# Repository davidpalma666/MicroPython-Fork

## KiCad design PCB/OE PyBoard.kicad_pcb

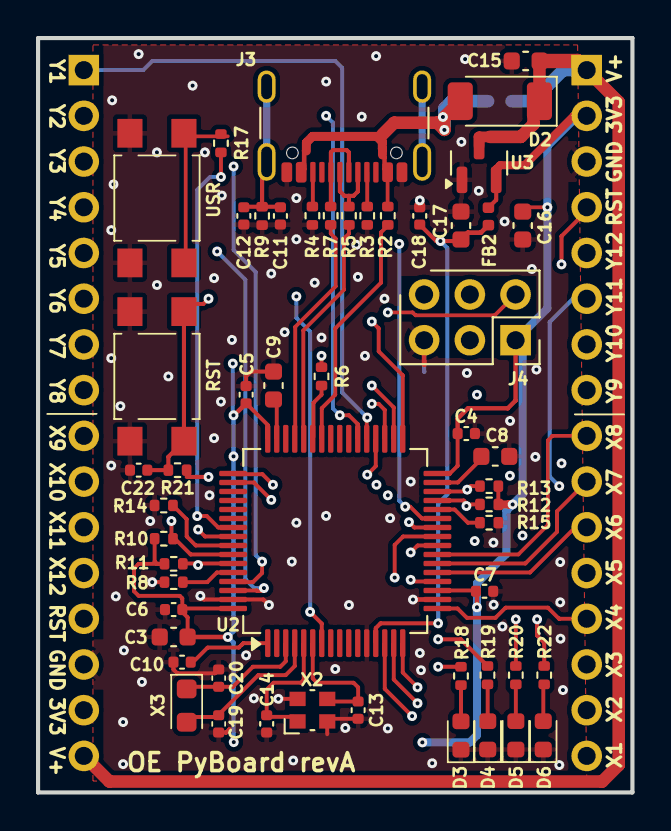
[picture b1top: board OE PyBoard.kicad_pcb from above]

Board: 4 copper layers, 33.0 x 41.9 mm, 56 parts (1 on the bottom side), 59 nets.

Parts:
C3, C16, C17: 4.7uF; C_0603_1608Metric
C4, C5, C6, C7, C10, C12, C18, C22: 100nF; C_0402_1005Metric
C8, C9, C15: 2.2uF; C_0603_1608Metric
C11: 4.7nF; C_0402_1005Metric
C13, C14, C19, C20: 12pF; C_0402_1005Metric
D2: SM5817PL; D_SOD-128
D3: LED-RED; LED_0603_1608Metric
D4: LED-GREEN; LED_0603_1608Metric
D5: LED-YELLOW; LED_0603_1608Metric
D6: LED-BLUE; LED_0603_1608Metric
FB2: 1k@100MHz; L_0402_1005Metric
J3: USB4105-GF-A; USB_C_Receptacle_GCT_USB4105-xx-A_16P_TopMnt_Horizontal
J4: Conn_02x03_Odd_Even; PinSocket_2x03_P2.54mm_Vertical
J6, J7: Conn_01x08; PinHeader_1x16_P2.54mm_Vertical
JP2: 0R; SolderJumper-2_P1.3mm_Open_RoundedPad1.0x1.5mm
R2, R18, R19, R20: 560R; R_0402_1005Metric
R3, R4: 5.1k; R_0402_1005Metric
R5, R7: 27R; R_0402_1005Metric
R6, R14, R15: 100k; R_0402_1005Metric
R8: 10k; R_0402_1005Metric
R9: 1M; R_0402_1005Metric
R10, R11, R12, R13, R17, R21: 4k7; R_0402_1005Metric
R22: 270R; R_0402_1005Metric
RST2: SW_SPST; SW_SPST_TL3305B
U2: STM32F405RGT6; LQFP-64_10x10mm_P0.5mm
U3: MCP1700T; SOT-23
USR2: SW_SPST; SW_SPST_TL3305B
X2: 12 MHz; Crystal_SMD_Abracon_ABM10-4Pin_2.5x2.0mm
X3: 32.768 kHz; Crystal_SMD_2012-2Pin_2.0x1.2mm_HandSoldering

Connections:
+3V3: C3.1, C4.1, C5.1, C6.1, C7.1, C16.1, FB2.1, J4.1, J6.15, J7.2, R6.1, R10.1, R11.1, R12.1, R13.1, R21.2, U2.19 (VDD), U2.32 (VDD), U2.48 (VDD), U2.64 (VDD), U3.2 (VO)
/B: D6.2 (A), R22.2
/BOOT0: R8.1, U2.60 (BOOT0)
/CC1: J3.A5 (CC1), R3.1
/CC2: J3.B5 (CC2), R4.1
/D+: J3.A6 (D+), J3.B6 (D+), R7.2
/D-: J3.A7 (D-), J3.B7 (D-), R5.2
/G: D4.2 (A), R19.2
/N1: C20.1, U2.3 (PC14-OSC32_IN), X3.1
/N2: C19.1, U2.4 (PC15-OSC32_OUT), X3.2
/N3: C14.1, U2.5 (PH0-OSC_IN), X2.1
/N4: C13.1, U2.6 (PH1-OSC_OUT), X2.3
/PA0-X1: J7.16, U2.14 (PA0)
/PA1-X2: J7.15, U2.15 (PA1)
/PA2-X3: J7.14, U2.16 (PA2)
/PA3-X4: J7.13, U2.17 (PA3)
/PA4-X5: J7.12, U2.20 (PA4)
/PA5-X6: J7.11, U2.21 (PA5)
/PA6-X7: J7.10, U2.22 (PA6)
/PA7-X8: J7.9, U2.23 (PA7)
/PA9-VBUS: R2.1, U2.42 (PA9)
/PA10-ID: R6.2, U2.43 (PA10)
/PA14-JTCK: J4.2, R19.1, U2.49 (PA14)
/PA15-JTDI: J4.6, R20.1, U2.50 (PA15)
/PB0-Y11: J7.6, U2.26 (PB0)
/PB1-Y12: J7.5, U2.27 (PB1)
/PB2-BOOT1-MMA-INT: R15.1, U2.28 (PB2)
/PB3-SW1: R17.1, U2.55 (PB3)
/PB4-NJTRST: J4.3, R22.1, U2.56 (PB4)
/PB5-MMA_AVDD: R14.1, U2.57 (PB5)
/PB6-JTDO: J4.4, R18.1
/PB6-SCL-X9: J6.9, R10.2, U2.58 (PB6)
/PB7-SDA-X10: J6.10, R11.2, U2.59 (PB7)
/PB8-Y3: J6.3, U2.61 (PB8)
/PB9-Y4: J6.4, U2.62 (PB9)
/PB10-Y9: J7.8, R12.2, U2.29 (PB10)
/PB11-Y10: J7.7, R13.2, U2.30 (PB11)
/PB12-Y5: J6.5, U2.33 (PB12)
/PB13-Y6: J6.6, U2.34 (PB13)
/PB14-Y7: J6.7, U2.35 (PB14)
/PB15-Y8: J6.8, U2.36 (PB15)
/PC4-X11: J6.11, U2.24 (PC4)
/PC5-X12: J6.12, U2.25 (PC5)
/PC6-Y1: J6.1, U2.37 (PC6)
/PC7-Y2: J6.2, U2.38 (PC7)
/R: D3.2 (A), R18.2
/RST-SW: C22.1, J6.13, J7.4, R21.1, RST2.1, U2.7 (~NRST)
/USB_N: R5.1, U2.44 (PA11)
/USB_P: R7.1, U2.45 (PA12)
/USR-SW: R17.2, USR2.1
/VDDA: C17.1, C18.1, FB2.2, U2.13 (VDDA)
/Y: D5.2 (A), R20.2
GND: C3.2, C4.2, C5.2, C6.2, C7.2, C8.2, C9.2, C10.2, C11.2, C12.1, C13.2, C14.2, C15.2, C16.2, C17.2, C18.2, C19.2, C20.2, C22.2, D3.1 (K), D4.1 (K), D5.1 (K), D6.1 (K), J3.A1 (GND), J3.A12 (GND), J3.B1 (GND), J3.B12 (GND), J4.5, J6.14, J7.3, R3.2, R4.2, R8.2, R9.1, R14.2, R15.2, RST2.2, U2.12 (VSSA), U2.18 (VSS), U2.63 (VSS), U3.1 (GND), USR2.2, X2.2, X2.4
unnamed: C11.1, C12.2, J3.S1 (SHIELD), R9.2
unnamed: C8.1, U2.31 (VCAP_1)
unnamed: C9.1, U2.47 (VCAP_2)
V+: C15.1, D2.1 (K), J6.16, J7.1, JP2.2 (B), U3.3 (VI)
VBAT: C10.1, U2.1 (VBAT)
VBUS: D2.2 (A), J3.A4 (VBUS), J3.A9 (VBUS), J3.B4 (VBUS), J3.B9 (VBUS), JP2.1 (A), R2.2

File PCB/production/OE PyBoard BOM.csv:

#;Qty;Reference;Value;Exclude from BOM;DNP;OEPSPN;MPN;Footprint
1;1;C11;4.7nF;;;OEPS010017;885012205084;Capacitor_SMD:C_0402_1005Metric
2;4;C13,C14,C19,C20;12pF;;;OEPS010086;GRM1555C1H120JA01D;Capacitor_SMD:C_0402_1005Metric
3;3;C3,C16,C17;4.7uF;;;OEPS010018;C1608X6S1C475K080AC;Capacitor_SMD:C_0603_1608Metric
4;8;C4,C5,C6,C7,C10,C12,C18,C22;100nF;;;OEPS010016;CGA2B3X7R1H104K050BB;Capacitor_SMD:C_0402_1005Metric
5;3;C8,C9,C15;2.2uF;;;OEPS010075;GRM188R61E225KA12D;Capacitor_SMD:C_0603_1608Metric
6;1;D2;SM5817PL;;;OEPS030030;SM5817PL-TP;Diode_SMD:D_SOD-128
7;1;D3;LED-RED;;;OEPS030006;5975004407F;LED_SMD:LED_0603_1608Metric
8;1;D4;LED-GREEN;;;OEPS030032;LSM0603453V;LED_SMD:LED_0603_1608Metric
9;1;D5;LED-YELLOW;;;OEPS030043;5990040007F;LED_SMD:LED_0603_1608Metric
10;1;D6;LED-BLUE;;;OEPS030042;5988D90107F;LED_SMD:LED_0603_1608Metric
11;1;FB2;1k@100MHz;;;OEPS040013;BLM15HD102SN1D;Inductor_SMD:L_0402_1005Metric
12;1;J3;USB4105-GF-A;;;OEPS070105;USB4105-GF-A;Connector_USB:USB_C_Receptacle_GCT_USB4105-xx-A_16P_TopMnt_Horizontal
13;1;J4;Conn_02x03_Odd_Even;;DNP;OEPS070015;67996-206HLF;Connector_PinSocket_2.54mm:PinSocket_2x03_P2.54mm_Vertical
14;2;J6,J7;Conn_01x08;;;OEPS070110;SAM1087-16-ND;Connector_PinHeader_2.54mm:PinHeader_1x16_P2.54mm_Vertical
15;1;R8;10k;;;OEPS020013;ERJ-2RKF1002X;Resistor_SMD:R_0402_1005Metric
16;1;R9;1M;;;OEPS020026;CRCW04021M00FKED;Resistor_SMD:R_0402_1005Metric
17;1;R22;270R;;;OEPS020060;CRCW0402270RFKEDC;Resistor_SMD:R_0402_1005Metric
18;6;R10,R11,R12,R13,R17,R21;4k7;;;OEPS020010;ERJ-2RKF4701X;Resistor_SMD:R_0402_1005Metric
19;4;R2,R18,R19,R20;560R;;;OEPS020193;CRCW0402560RFKED;Resistor_SMD:R_0402_1005Metric
20;2;R3,R4;5.1k;;;OEPS020173;ERJ-2RKF5101X;Resistor_SMD:R_0402_1005Metric
21;2;R5,R7;22R;;;OEPS020170;RMCF0402FT27R0;Resistor_SMD:R_0402_1005Metric
22;3;R6,R14,R15;100k;;;OEPS020051;AC0402FR-07100KL;Resistor_SMD:R_0402_1005Metric
23;2;RST2,USR2;SW_SPST;;;OEPS100061;TL3305BF260QG;Button_Switch_SMD:SW_SPST_TL3305B
24;1;U2;STM32F405RGT6;;;OEPS080178;STM32F405RGT6;Package_QFP:LQFP-64_10x10mm_P0.5mm
25;1;U3;MCP1700T;;;OEPS080153;MCP1700T-3302E/TT;Package_TO_SOT_SMD:SOT-23
26;1;X2;12 MHz;;;OEPS100059;ABM8AIG-12.000MHZ-12-2Z-T3;Crystal:Crystal_SMD_Abracon_ABM10-4Pin_2.5x2.0mm
27;1;X3;32.768 kHz;;;OEPS100051;9HT11-32.768KBZF-T;Crystal:Crystal_SMD_2012-2Pin_2.0x1.2mm_HandSoldering

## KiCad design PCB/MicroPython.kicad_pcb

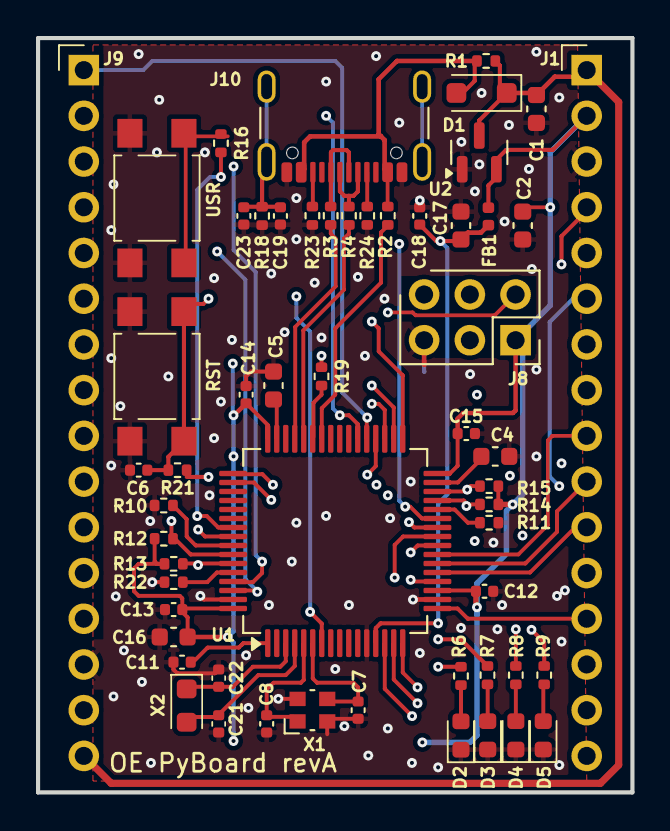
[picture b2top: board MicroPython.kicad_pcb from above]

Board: 4 copper layers, 33.0 x 41.9 mm, 56 parts (0 on the bottom side), 59 nets.

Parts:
C1, C4, C5: 2u2; C_0603_1608Metric
C2: 4u7; C_0603_1608Metric
C6, C11, C12, C13, C14, C15, C18: 100n; C_0402_1005Metric
C7, C8, C21, C22: 12pF; C_0402_1005Metric
C16, C17: 4.7u; C_0603_1608Metric
C19: 4.7nF; C_0402_1005Metric
C23: 100nF; C_0402_1005Metric
D1: SM5817PL; D_SOD-123F
D2: LED-RED; LED_0603_1608Metric
D3: LED-GREEN; LED_0603_1608Metric
D4: LED-YELLOW; LED_0603_1608Metric
D5: LED-BLUE; LED_0603_1608Metric
FB1: 1k@100MHz; L_0402_1005Metric
J1, J9: Conn_01x08; PinHeader_1x16_P2.54mm_Vertical
J8: Conn_02x03_Odd_Even; PinSocket_2x03_P2.54mm_Vertical
J10: USB4105-GF-A; USB_C_Receptacle_GCT_USB4105-xx-A_16P_TopMnt_Horizontal
R1: 0R; R_0402_1005Metric
R2, R6, R7, R8: 560R; R_0402_1005Metric
R3, R4: 22R; R_0402_1005Metric
R9: 270R; R_0402_1005Metric
R10, R11, R19: 100k; R_0402_1005Metric
R12, R13, R14, R15, R16, R21: 4k7; R_0402_1005Metric
R18: 1M; R_0402_1005Metric
R22: 10k; R_0402_1005Metric
R23, R24: 5.1k; R_0402_1005Metric
RST1: SW_SPST; SW_SPST_TL3305B
U1: STM32F405RGT6; LQFP-64_10x10mm_P0.5mm
U2: MCP1700T; SOT-23
USR1: SW_SPST; SW_SPST_TL3305B
X1: 12 MHz; Crystal_SMD_Abracon_ABM10-4Pin_2.5x2.0mm
X2: 32.768 kHz; Crystal_SMD_2012-2Pin_2.0x1.2mm_HandSoldering

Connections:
+3V3: C2.1, C12.1, C13.1, C14.1, C15.1, C16.1, FB1.1, J1.2, J8.1, J9.15, R12.1, R13.1, R14.1, R15.1, R19.1, R21.2, U1.19 (VDD), U1.32 (VDD), U1.48 (VDD), U1.64 (VDD), U2.2 (VO)
/B: D5.2 (A), R9.2
/BOOT0: R22.1, U1.60 (BOOT0)
/CC1: J10.A5 (CC1), R24.1
/CC2: J10.B5 (CC2), R23.1
/D+: J10.A6 (D+), J10.B6 (D+), R3.2
/D-: J10.A7 (D-), J10.B7 (D-), R4.2
/G: D3.2 (A), R7.2
/N1: C22.1, U1.3 (PC14-OSC32_IN), X2.1
/N2: C21.1, U1.4 (PC15-OSC32_OUT), X2.2
/N3: C8.1, U1.5 (PH0-OSC_IN), X1.1
/N4: C7.1, U1.6 (PH1-OSC_OUT), X1.3
/PA0-X1: J1.16, U1.14 (PA0)
/PA1-X2: J1.15, U1.15 (PA1)
/PA2-X3: J1.14, U1.16 (PA2)
/PA3-X4: J1.13, U1.17 (PA3)
/PA4-X5: J1.12, U1.20 (PA4)
/PA5-X6: J1.11, U1.21 (PA5)
/PA6-X7: J1.10, U1.22 (PA6)
/PA7-X8: J1.9, U1.23 (PA7)
/PA9-VBUS: R2.1, U1.42 (PA9)
/PA10-ID: R19.2, U1.43 (PA10)
/PA14-JTCK: J8.2, R7.1, U1.49 (PA14)
/PA15-JTDI: J8.6, R8.1, U1.50 (PA15)
/PB0-Y11: J1.6, U1.26 (PB0)
/PB1-Y12: J1.5, U1.27 (PB1)
/PB2-BOOT1-MMA-INT: R11.1, U1.28 (PB2)
/PB3-SW1: R16.1, U1.55 (PB3)
/PB4-NJTRST: J8.3, R9.1, U1.56 (PB4)
/PB5-MMA_AVDD: R10.1, U1.57 (PB5)
/PB6-JTDO: J8.4, R6.1
/PB6-SCL-X9: J9.9, R12.2, U1.58 (PB6)
/PB7-SDA-X10: J9.10, R13.2, U1.59 (PB7)
/PB8-Y3: J9.3, U1.61 (PB8)
/PB9-Y4: J9.4, U1.62 (PB9)
/PB10-Y9: J1.8, R14.2, U1.29 (PB10)
/PB11-Y10: J1.7, R15.2, U1.30 (PB11)
/PB12-Y5: J9.5, U1.33 (PB12)
/PB13-Y6: J9.6, U1.34 (PB13)
/PB14-Y7: J9.7, U1.35 (PB14)
/PB15-Y8: J9.8, U1.36 (PB15)
/PC4-X11: J9.11, U1.24 (PC4)
/PC5-X12: J9.12, U1.25 (PC5)
/PC6-Y1: J9.1, U1.37 (PC6)
/PC7-Y2: J9.2, U1.38 (PC7)
/R: D2.2 (A), R6.2
/RST-SW: C6.1, J1.4, J9.13, R21.1, RST1.1, U1.7 (~NRST)
/USB_N: R4.1, U1.44 (PA11)
/USB_P: R3.1, U1.45 (PA12)
/USR-SW: R16.2, USR1.1
/VDDA: C17.1, C18.1, FB1.2, U1.13 (VDDA)
/Y: D4.2 (A), R8.2
GND: C1.2, C2.2, C4.2, C5.2, C6.2, C7.2, C8.2, C11.2, C12.2, C13.2, C14.2, C15.2, C16.2, C17.2, C18.2, C19.2, C21.2, C22.2, C23.1, D2.1 (K), D3.1 (K), D4.1 (K), D5.1 (K), J1.3, J8.5, J9.14, J10.A1 (GND), J10.A12 (GND), J10.B1 (GND), J10.B12 (GND), R10.2, R11.2, R18.1, R22.2, R23.2, R24.2, RST1.2, U1.12 (VSSA), U1.18 (VSS), U1.63 (VSS), U2.1 (GND), USR1.2, X1.2, X1.4
unnamed: C19.1, C23.2, J10.S1 (SHIELD), R18.2
unnamed: C4.1, U1.31 (VCAP_1)
unnamed: C5.1, U1.47 (VCAP_2)
VBAT: C11.1, U1.1 (VBAT)
VBUS: D1.2 (A), J10.A4 (VBUS), J10.A9 (VBUS), J10.B4 (VBUS), J10.B9 (VBUS), R1.1, R2.2
VIN: C1.1, D1.1 (K), J1.1, J9.16, R1.2, U2.3 (VI)

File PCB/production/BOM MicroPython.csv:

"#","Reference","Qty","Value","OEPSPN","MPN","Footprint","notes"
"1","X1","1","12 MHz","OEPS100059","ABM8AIG-12.000MHZ-12-2Z-T3","Crystal:Crystal_SMD_Abracon_ABM10-4Pin_2.5x2.0mm",""
"2","SW1,SW2","2","SW_SPST","OEPS100061","TL3305BF260QG","Button_Switch_SMD:SW_SPST_TL3305B",""
"3","R23,R24","2","5.1k","OEPS020173","ERJ-2RKF5101X","Resistor_SMD:R_0402_1005Metric",""
"4","R22","1","10k","OEPS020013","ERJ-2RKF1002X","Resistor_SMD:R_0402_1005Metric",""
"5","R12,R13,R14,R15,R16,R21","6","4k7","OEPS020026","CRCW04021M00FKED","Resistor_SMD:R_0402_1005Metric",""
"6","R10,R11,R19","3","100k","OEPS020051","AC0402FR-07100KL","Resistor_SMD:R_0402_1005Metric",""
"7","R9","1","270R","OEPS020060","CRCW0402270RFKEDC","Resistor_SMD:R_0402_1005Metric",""
"8","R3,R4","2","22R","OEPS020170","RMCF0402FT27R0","Resistor_SMD:R_0402_1005Metric",""
"9","R2,R6,R7,R8","4","560R","OEPS020193","CRCW0402560RFKED","Resistor_SMD:R_0402_1005Metric",""
"10","J1,J9","2","Conn_01x08","OEPS070110","SAM1087-16-ND","Connector_PinHeader_2.54mm:PinHeader_1x16_P2.54mm_Vertical",""
"11","FB1","1","1k@100MHz","OEPS040013","BLM15HD102SN1D","Inductor_SMD:L_0402_1005Metric",""
"12","D5","1","LED-BLUE","OEPS030042","5988D90107F","LED_SMD:LED_0603_1608Metric",""
"13","D4","1","LED-YELLOW","OEPS030043","5990040007F","LED_SMD:LED_0603_1608Metric",""
"14","D3","1","LED-GREEN","OEPS030032","LSM0603453V","LED_SMD:LED_0603_1608Metric",""
"15","D2","1","LED-RED","OEPS030006","5975004407F","LED_SMD:LED_0603_1608Metric",""
"16","D1","1","SM5817PL","OEPS030030","SM5817PL-TP","Diode_SMD:D_SOD-123F","original part: 1N5819"
"17","C16,C17","2","4.7u","OEPS010018","C1608X6S1C475K080AC","Capacitor_SMD:C_0603_1608Metric",""
"18","C7,C8","2","12pF","OEPS010086","GRM1555C1H120JA01D","Capacitor_SMD:C_0402_1005Metric",""
"19","C6,C11,C12,C13,C14,C15,C18","7","100n","OEPS010016","CGA2B3X7R1H104K050BB","Capacitor_SMD:C_0402_1005Metric",""
"20","C2","1","4u7","OEPS010018","C1608X6S1C475K080AC","Capacitor_SMD:C_0603_1608Metric",""
"21","C1,C4,C5","3","2u2","OEPS010075","GRM188R61E225KA12D","Capacitor_SMD:C_0603_1608Metric",""
"22","J10","1","USB4105-GF-A","OEPS070105","USB4105-GF-A","Connector_USB:USB_C_Receptacle_GCT_USB4105-xx-A_16P_TopMnt_Horizontal",""
"23","U2","1","MCP1700T","OEPS080153","MCP1700T-3302E/TT","Package_TO_SOT_SMD:SOT-23",""
"24","U1","1","STM32F405RGT6","OEPS080178","STM32F405RGT6","Package_QFP:LQFP-64_10x10mm_P0.5mm",""
"25","R18","1","1M","OEPS020026","CRCW04021M00FKED","Resistor_SMD:R_0402_1005Metric",""
"26","C23","1","100nF","OEPS010016","CGA2B3X7R1H104K050BB","Capacitor_SMD:C_0402_1005Metric",""
"27","C19","1","4.7nF","OEPS010017","885012205084","Capacitor_SMD:C_0402_1005Metric",""

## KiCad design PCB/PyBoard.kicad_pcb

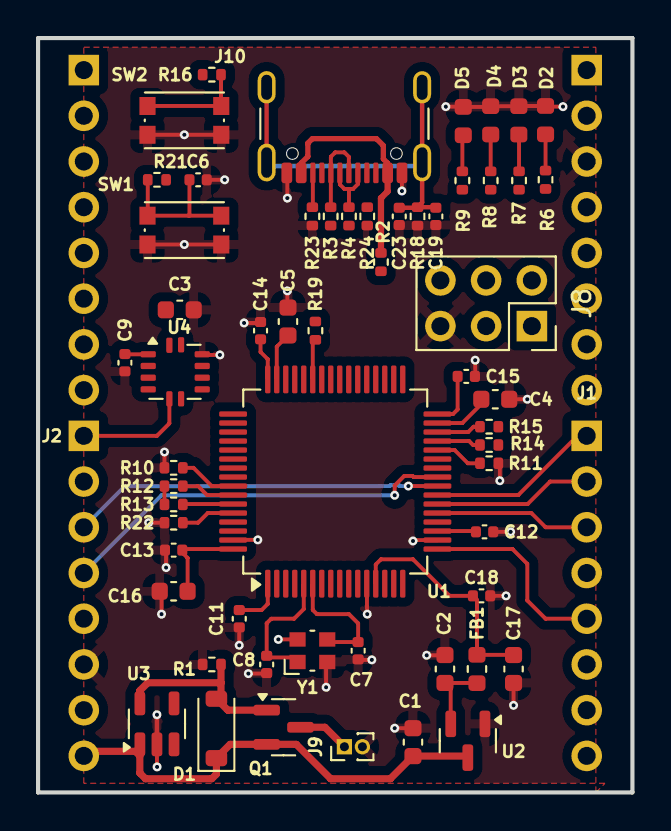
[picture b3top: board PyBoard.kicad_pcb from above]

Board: 2 copper layers, 33.0 x 41.9 mm, 61 parts (0 on the bottom side), 58 nets.

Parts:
C1, C3, C4, C5: 2u2; C_0603_1608Metric
C2: 4u7; C_0603_1608Metric
C6, C9, C11, C12, C13, C14, C15, C18: 100n; C_0402_1005Metric
C7, C8: 12p; C_0402_1005Metric
C16, C17: 4.7u; C_0603_1608Metric
C19: 4.7nF; C_0402_1005Metric
C23: 100nF; C_0402_1005Metric
D1: MSE1PB-M3/89A; D_SOD-123
D2: LED-RED; LED_0603_1608Metric
D3: LED-GREEN; LED_0603_1608Metric
D4: LED-YELLOW; LED_0603_1608Metric
D5: LED-BLUE; LED_0603_1608Metric
FB1: 1k; L_0603_1608Metric
J1, J2, J6, J7: Conn_01x08; PinHeader_1x08_P2.54mm_Vertical
J8: Conn_02x03_Odd_Even; PinSocket_2x03_P2.54mm_Vertical
J9: Conn_01x02; PinHeader_1x02_P1.00mm_Vertical
J10: USB4105-GF-A; USB_C_Receptacle_GCT_USB4105-xx-A_16P_TopMnt_Horizontal
Q1: DMP2160UW; SOT-23
R1, R10, R11, R19: 100k; R_0402_1005Metric
R2, R6, R7, R8: 560R; R_0402_1005Metric
R3, R4: 22R; R_0402_1005Metric
R9: 220R; R_0402_1005Metric
R12, R13, R14, R15, R16, R21: 4k7; R_0402_1005Metric
R18: 1M; R_0402_1005Metric
R22: 10k; R_0402_1005Metric
R23, R24: 5.1k; R_0402_1005Metric
SW1, SW2: SW_MEC_5E; SW_Push_1P1T_NO_CK_KMR2
U1: STM32F405RGT6; LQFP-64_10x10mm_P0.5mm
U2: MCP1700T; SOT-23
U3: MIC2005A-1YM5; SOT-23-5
U4: FXLS8971CFR1; LQFN-12-3x3mm_P0.65mm
Y1: 12 MHz; Crystal_SMD_Abracon_ABM10-4Pin_2.5x2.0mm

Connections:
+3V3: C2.1, C9.1, C12.1, C13.1, C14.1, C15.1, C16.1, FB1.1, J2.7, J7.2, J8.1, R12.1, R13.1, R14.1, R15.1, R19.1, R21.2, U1.19 (VDD), U1.32 (VDD), U1.48 (VDD), U1.64 (VDD), U2.2 (VO), U4.1 (VDD)
/B: D5.2 (A), R9.2
/BOOT0: R22.1, U1.60 (BOOT0)
/CC1: J10.A5 (CC1), R24.1
/CC2: J10.B5 (CC2), R23.1
/D+: J10.A6 (D+), J10.B6 (D+), R3.2
/D-: J10.A7 (D-), J10.B7 (D-), R4.2
/G: D3.2 (A), R7.2
/N3: C8.1, U1.5 (PH0-OSC_IN), Y1.1
/N4: C7.1, U1.6 (PH1-OSC_OUT), Y1.3
/PA0-X1: J1.8, U1.14 (PA0)
/PA1-X2: J1.7, U1.15 (PA1)
/PA2-X3: J1.6, U1.16 (PA2)
/PA3-X4: J1.5, U1.17 (PA3)
/PA4-X5: J1.4, U1.20 (PA4)
/PA5-X6: J1.3, U1.21 (PA5)
/PA6-X7: J1.2, U1.22 (PA6)
/PA7-X8: J1.1, U1.23 (PA7)
/PA9-VBUS: R2.1, U1.42 (PA9)
/PA10-ID: R19.2, U1.43 (PA10)
/PA11-DM: R4.1, U1.44 (PA11)
/PA12-DP: R3.1, U1.45 (PA12)
/PA13-SWDIO: J8.2, R6.1, U1.46 (PA13)
/PA14-SWCLCK: J8.6, R7.1, U1.49 (PA14)
/PA15-TDI: R8.1, U1.50 (PA15)
/PB0-Y11: J7.6, U1.26 (PB0)
/PB1-Y12: J7.5, U1.27 (PB1)
/PB2-BOOT1-MMA-INT: R11.1, U1.28 (PB2)
/PB3-SW-X17: R16.1, U1.55 (PB3)
/PB4-TRST: R9.1, U1.56 (PB4), U3.3 (EN)
/PB5-MMA_AVDD: C3.1, R10.1, U1.57 (PB5)
/PB6-SCL-X9: J2.1, R12.2, U1.58 (PB6), U4.5 (SCL/SCLK)
/PB7-SDA-X10: J2.2, R13.2, U1.59 (PB7), U4.4 (SDA/SPI_MOSI)
/PB8-Y3: J6.3, U1.61 (PB8)
/PB9-Y4: J6.4, U1.62 (PB9)
/PB10-Y9: J7.8, R14.2, U1.29 (PB10)
/PB11-Y10: J7.7, R15.2, U1.30 (PB11)
/PB12-Y5: J6.5, U1.33 (PB12)
/PB13-Y6: J6.6, U1.34 (PB13)
/PB14-Y7: J6.7, U1.35 (PB14)
/PB15-Y8: J6.8, U1.36 (PB15)
/PC4-X11: J2.3, U1.24 (PC4)
/PC5-X12: J2.4, U1.25 (PC5)
/PC6-Y1: J6.1, U1.37 (PC6)
/PC7-Y2: J6.2, U1.38 (PC7)
/R: D2.2 (A), R6.2
/RST-SW: C6.1, J2.5, J7.4, J8.4, R21.1, SW1.1, U1.7 (~NRST)
/USR-SW: R16.2, SW2.1
/VDDA: C17.1, C18.1, FB1.2, U1.13 (VDDA)
/Y: D4.2 (A), R8.2
GND: C1.2, C2.2, C3.2, C4.2, C5.2, C6.2, C7.2, C8.2, C9.2, C11.2, C12.2, C13.2, C14.2, C15.2, C16.2, C17.2, C18.2, C19.2, C23.1, D2.1 (K), D3.1 (K), D4.1 (K), D5.1 (K), J2.6, J7.3, J8.5, J9.2, J10.A1 (GND), J10.A12 (GND), J10.B1 (GND), J10.B12 (GND), R1.2, R10.2, R11.2, R18.1, R22.2, R23.2, R24.2, SW1.2, SW2.2, U1.12 (VSSA), U1.18 (VSS), U1.63 (VSS), U2.1 (GND), U3.2 (GND), U4.10 (GND), Y1.2, Y1.4
unnamed: C19.1, C23.2, J10.S1 (SHIELD), R18.2
unnamed: C4.1, U1.31 (VCAP_1)
unnamed: C5.1, U1.47 (VCAP_2)
V+: C1.1, D1.1 (K), J2.8, J7.1, Q1.2 (S), U2.3 (VI), U3.1 (VIN)
VBAT: J9.1, Q1.3 (D)
VBUS: D1.2 (A), J10.A4 (VBUS), J10.A9 (VBUS), J10.B4 (VBUS), J10.B9 (VBUS), Q1.1 (G), R1.1, R2.2, U3.5 (VOUT)
VBackup: C11.1, U1.1 (VBAT)

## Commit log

2025-09-01 1º commit de projecto
    - desenho de Scgm & PCB já iniciado em Kicad-v.9.0.4
    - dúvidas ainda a esclarecer a nível de schm
    - folder auxiliar com antigas versões do projecto, pinout etc
2025-09-02 actualizado/modificado nome de projecto - MicroPython
    - nome alterado para estar de acordo com folder de Projecto & Repositório no GitHub
    - desenho ainda em desenvolvimento
2025-09-04 MicroPython v.1.0
    MicroPython v.1.0
    - DRC=0
    - em falta alguns novos OEPSPN
2025-09-05 MicroPhython v.1.0
    - maior alterações a nivel do rail de PowerIn
    - retirado a andar de PFET - em versões anteriores e posteriores à PCB v.1.1 estes andares não exixtiam
    - realocação & re-routing na PCB do andar de PowerIn
    - DRC=0
2025-09-10 ficheiros de produção gerados
    - todos os componentes com OEPS & MPN
    - gerados ficheiros de produção \production
    - gerada BOM
2025-09-11 mudanças a partir de mudanças sugeridas pelo Filipe
    - projecto commited já com pequenas alterações do Filipe
2025-09-11 OE-PyBoard - revisão depois de avaliação Filipe
    - nome do projecto/ficheiros alterados para OE-PyBoard
    - Colocar OEPS logo para o bottom, e colocar no meio da board
    - X1: Mudar a referência para a parte de cima
    - udar o diode D1 para 2A & aumentar a secção das linhas VBUS
    - alterado o sinal VIN para V+, para ficar coerente com a board original
    - passar X2 & C21 & C22 para assembled
2025-09-12 corrigido denominação de unidades nos valores de componentes
    - gerados novos ficheiros de produção
2025-09-12 modificada refª de origem para P&P
    - modificada refª de origem de P&P p/a canto inferior esqº
    - gerados novos ficheiros de P&P
    - outros ficheiros Gerbers de produção sem modificações
2025-09-12 adicionado ficheiro de netlist
    - ficheiro de netlist \production\OE PyBoard.d356
2025-09-15 sincronia com mudanças q o Filipe fez
2025-09-15 correcção sobre modelos .step nos switches
